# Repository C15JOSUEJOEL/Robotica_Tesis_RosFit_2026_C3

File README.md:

# Robotica_Tesis_RosFit_2026_C3

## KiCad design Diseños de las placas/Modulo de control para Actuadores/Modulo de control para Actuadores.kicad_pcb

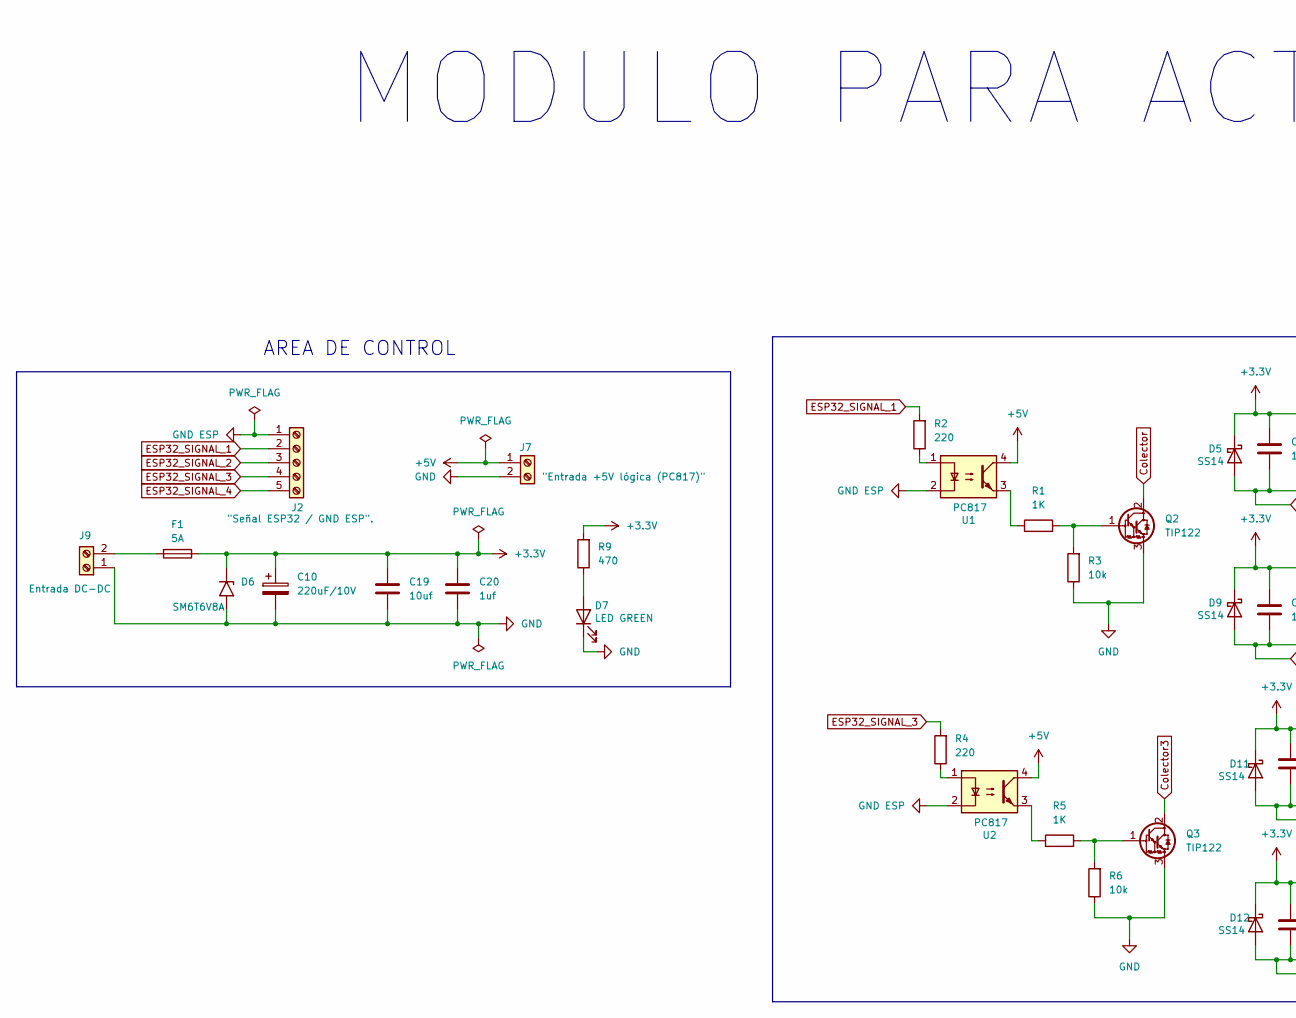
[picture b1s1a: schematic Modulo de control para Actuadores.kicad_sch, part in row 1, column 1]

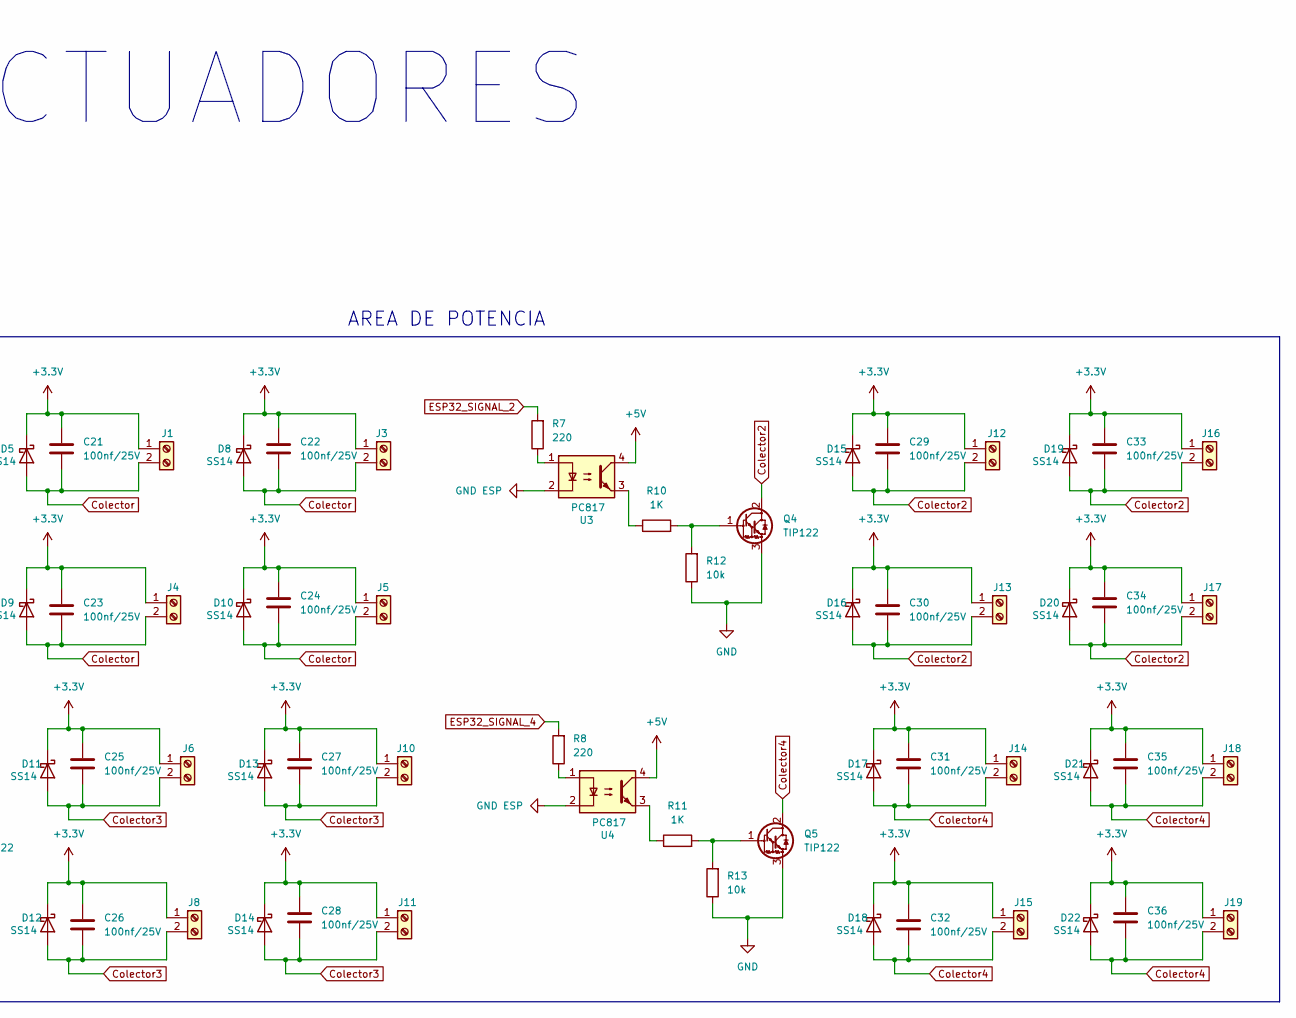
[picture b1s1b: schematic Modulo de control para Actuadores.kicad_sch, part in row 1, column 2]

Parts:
C10: 220uF/10V; CP_EIA-3528-21_Kemet-B
C19: 10uf; C_0603_1608Metric
C20: 1uf; C_0603_1608Metric
C21, C22, C23, C24, C25, C26, C27, C28, C29, C30, C31, C32, C33, C34, C35, C36: 100nf/25V; C_0805_2012Metric
D5, D8, D9, D10, D11, D12, D13, D14, D15, D16, D17, D18, D19, D20, D21, D22: SS14; D_SMA
D6: SM6T6V8A; D_SMB
D7: LED GREEN; LED_0603_1608Metric
F1: 5A; Fuse_1812_4532Metric
J1, J3, J4, J5, J6, J8, J10, J11, J12, J13, J14, J15, J16, J17, J18, J19: Screw_Terminal_01x02; TerminalBlock_MaiXu_MX126-5.0-02P_1x02_P5.00mm
J2: "Señal ESP32 / GND ESP".; TerminalBlock_MaiXu_MX126-5.0-05P_1x05_P5.00mm
J7: "Entrada +5V lógica (PC817)"; TerminalBlock_MaiXu_MX126-5.0-02P_1x02_P5.00mm
J9: Entrada DC-DC; TerminalBlock_MetzConnect_Type055_RT01502HDWU_1x02_P5.00mm_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
Q2, Q3, Q4, Q5: TIP122; TO-220-3_Vertical
R1, R5, R10, R11: 1K; R_1206_3216Metric_Pad1.30x1.75mm_HandSolder
R2, R4, R7, R8: 220; R_1206_3216Metric_Pad1.30x1.75mm_HandSolder
R3, R6, R12, R13: 10k; R_1206_3216Metric_Pad1.30x1.75mm_HandSolder
R9: 470; R_0603_1608Metric
U1, U2, U3, U4: PC817; DIP-4_W7.62mm

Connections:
+3.3V: C10.1, C19.1, C20.1, C21.1, C22.1, C23.1, C24.1, C25.1, C26.1, C27.1, C28.1, C29.1, C30.1, C31.1, C32.1, C33.1, C34.1, C35.1, C36.1, D5.1 (K), D6.1 (A1), D8.1 (K), D9.1 (K), D10.1 (K), D11.1 (K), D12.1 (K), D13.1 (K), D14.1 (K), D15.1 (K), D16.1 (K), D17.1 (K), D18.1 (K), D19.1 (K), D20.1 (K), D21.1 (K), D22.1 (K), F1.1, J1.1, J3.1, J4.1, J5.1, J6.1, J8.1, J10.1, J11.1, J12.1, J13.1, J14.1, J15.1, J16.1, J17.1, J18.1, J19.1, R9.2
+5V: J7.1, U1.4, U2.4, U3.4, U4.4
Colector: C21.2, C22.2, C23.2, C24.2, D5.2 (A), D8.2 (A), D9.2 (A), D10.2 (A), J1.2, J3.2, J4.2, J5.2, Q2.2 (C)
Colector2: C29.2, C30.2, C33.2, C34.2, D15.2 (A), D16.2 (A), D19.2 (A), D20.2 (A), J12.2, J13.2, J16.2, J17.2, Q4.2 (C)
Colector3: C25.2, C26.2, C27.2, C28.2, D11.2 (A), D12.2 (A), D13.2 (A), D14.2 (A), J6.2, J8.2, J10.2, J11.2, Q3.2 (C)
Colector4: C31.2, C32.2, C35.2, C36.2, D17.2 (A), D18.2 (A), D21.2 (A), D22.2 (A), J14.2, J15.2, J18.2, J19.2, Q5.2 (C)
ESP32_SIGNAL_1: J2.2, R2.2
ESP32_SIGNAL_2: J2.3, R7.2
ESP32_SIGNAL_3: J2.4, R4.2
ESP32_SIGNAL_4: J2.5, R8.2
GND: C10.2, C19.2, C20.2, D6.2 (A2), D7.1 (K), J7.2, J9.1, Q2.3 (E), Q3.3 (E), Q4.3 (E), Q5.3 (E), R3.1, R6.1, R12.1, R13.1
GND ESP: J2.1, U1.2, U2.2, U3.2, U4.2
unnamed: D7.2 (A), R9.1
unnamed: F1.2, J9.2
unnamed: Q2.1 (B), R1.2, R3.2
unnamed: Q3.1 (B), R5.2, R6.2
unnamed: Q4.1 (B), R10.2, R12.2
unnamed: Q5.1 (B), R11.2, R13.2
unnamed: R1.1, U1.3
unnamed: R2.1, U1.1
unnamed: R4.1, U2.1
unnamed: R5.1, U2.3
unnamed: R7.1, U3.1
unnamed: R8.1, U4.1
unnamed: R10.1, U3.3
unnamed: R11.1, U4.3

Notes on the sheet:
AREA DE POTENCIA
AREA DE CONTROL
MODULO PARA ACTUADORES

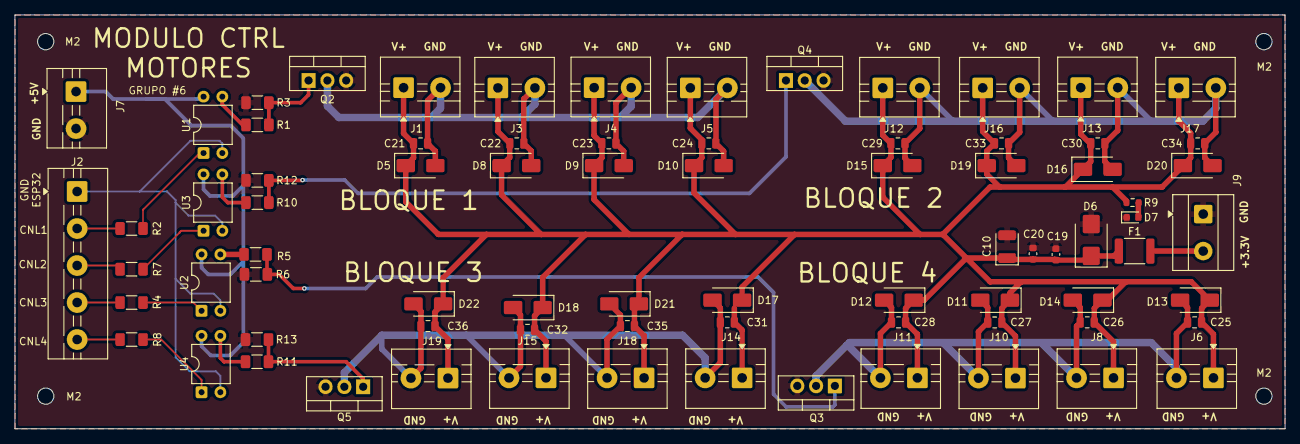
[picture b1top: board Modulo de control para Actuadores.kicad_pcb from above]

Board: 2 copper layers, 171.6 x 55.9 mm, 82 parts (0 on the bottom side), 26 nets.

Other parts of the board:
M2, M2#2, M2#3, M2#4: MountingHole_2.2mm_M2
